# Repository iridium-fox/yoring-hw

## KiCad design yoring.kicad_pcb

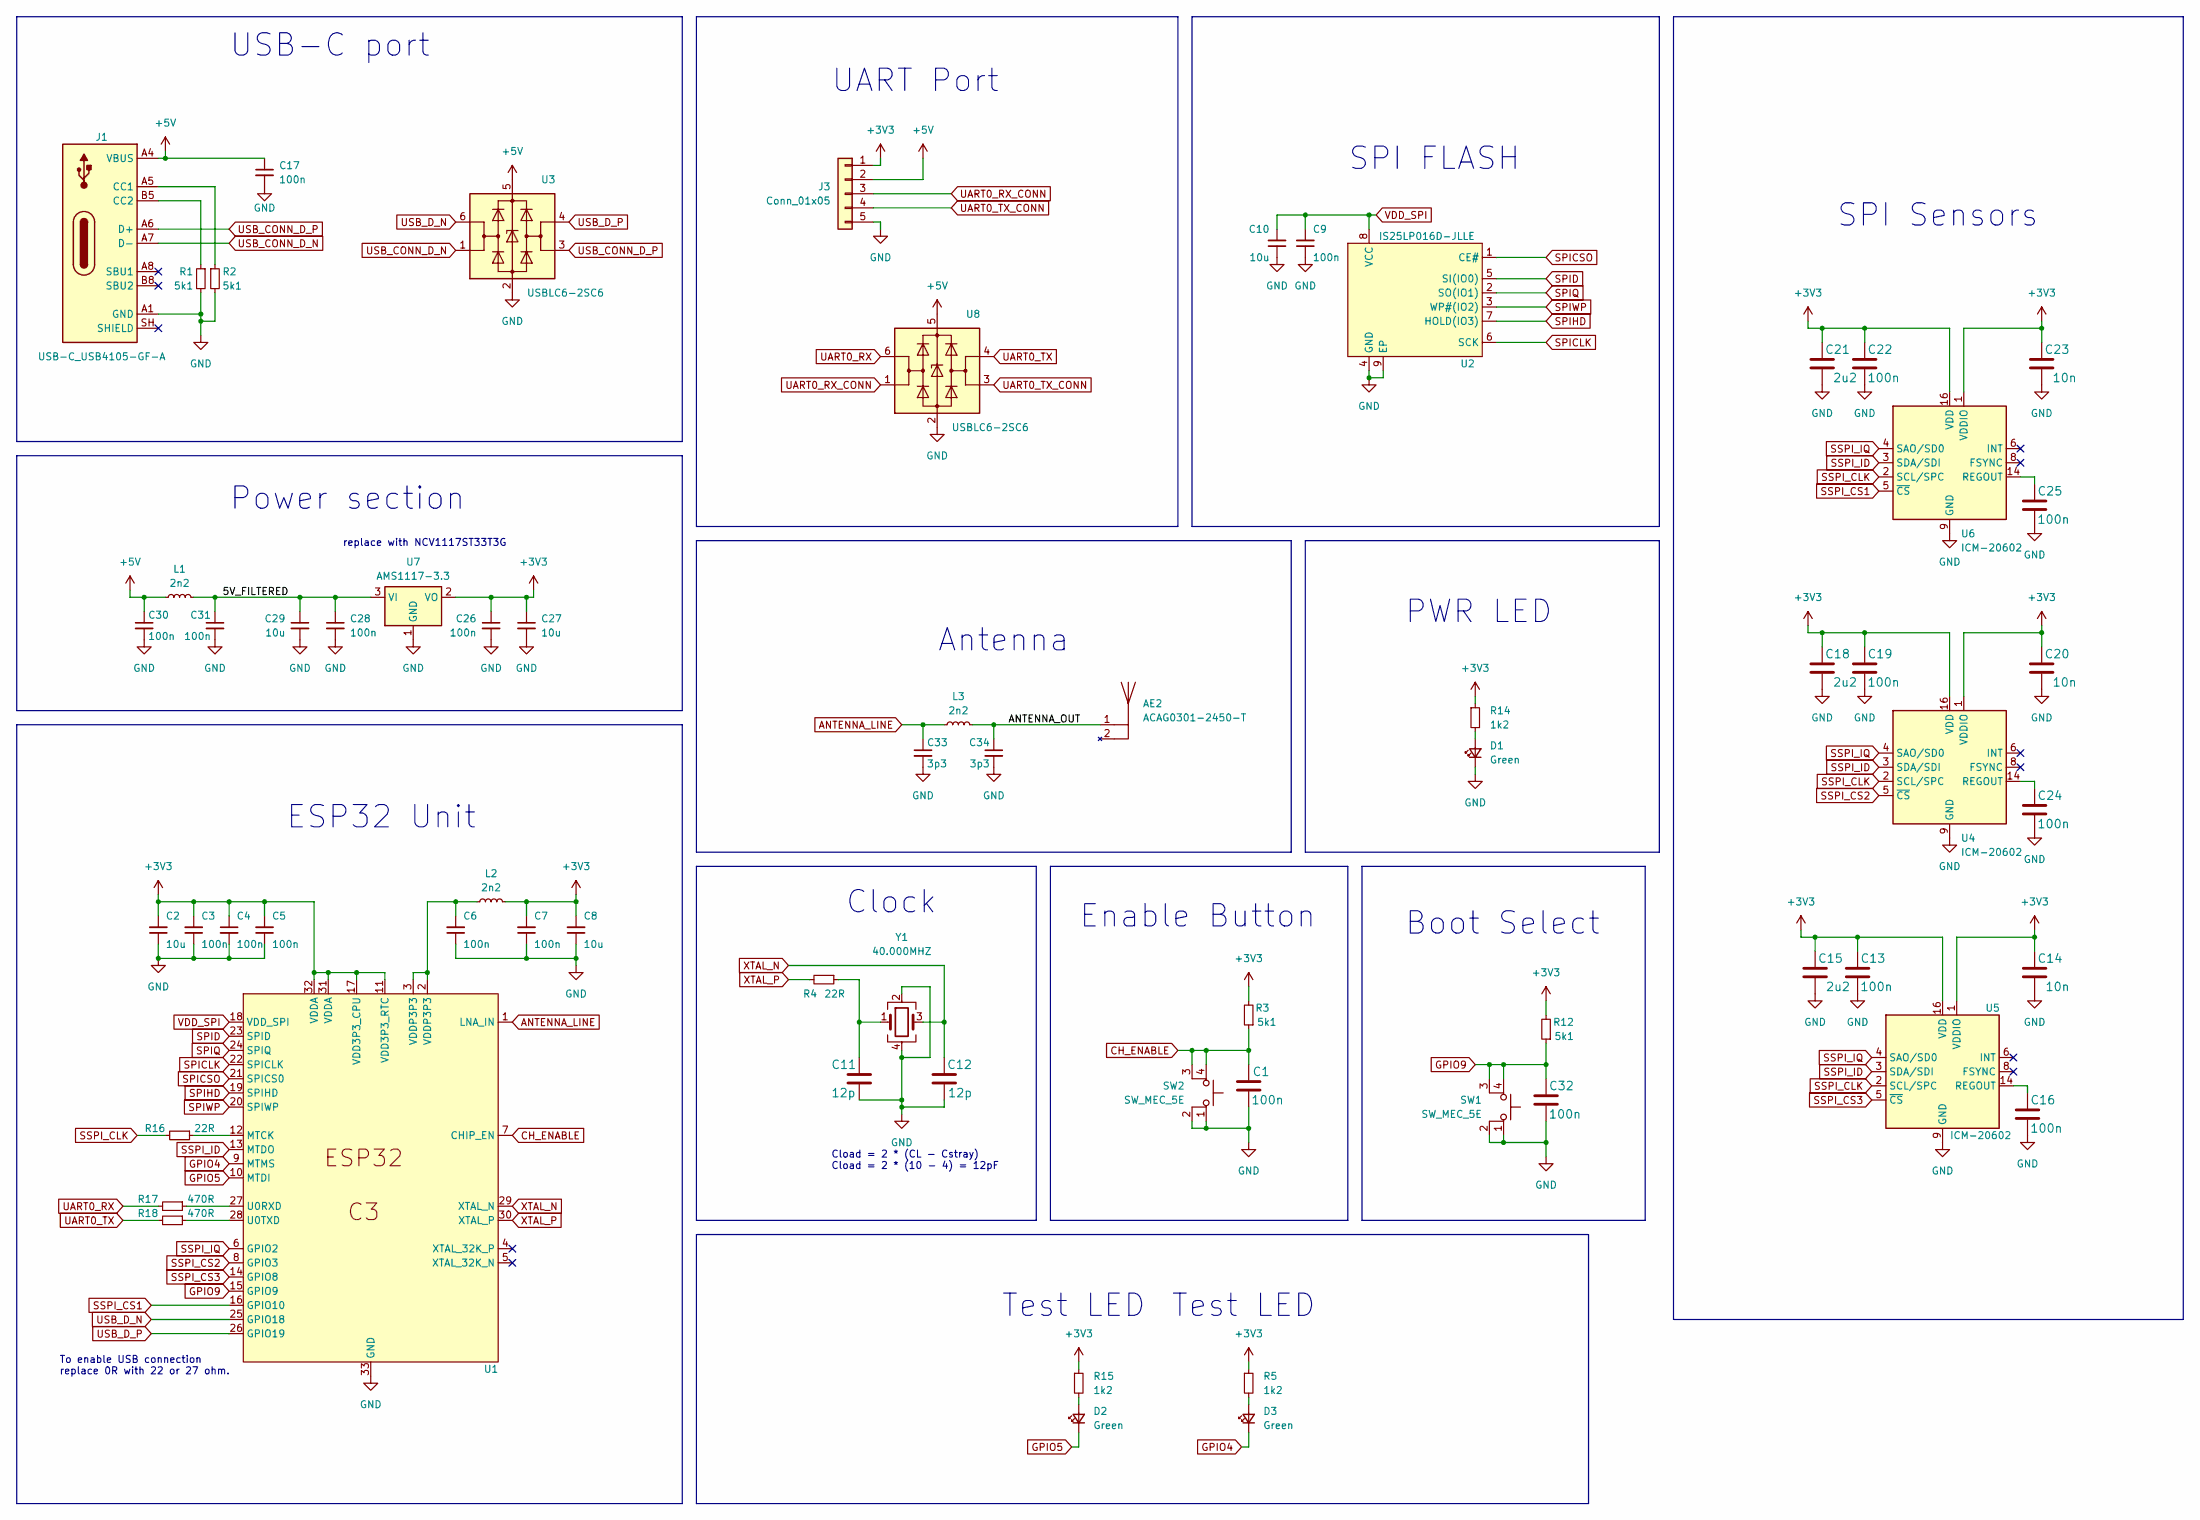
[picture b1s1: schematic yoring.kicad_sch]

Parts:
AE2: ACAG0301-2450-T; ANTC3216X130N
C1, C3, C4, C5, C6, C7, C9, C13, C16, C17, C19, C22, C24, C25, C26, C28, C30, C31, C32: 100n; C_0402_1005Metric_Pad0.74x0.62mm_HandSolder
C2, C8, C10, C27, C29: 10u; C_0603_1608Metric_Pad1.08x0.95mm_HandSolder
C11, C12: 12p; C_0402_1005Metric_Pad0.74x0.62mm_HandSolder
C14, C20, C23: 10n; C_0402_1005Metric_Pad0.74x0.62mm_HandSolder
C15, C18, C21: 2u2; C_0402_1005Metric_Pad0.74x0.62mm_HandSolder
C33, C34: 3p3; C_0402_1005Metric_Pad0.74x0.62mm_HandSolder
D1, D2, D3: Green; LED_0603_1608Metric_Pad1.05x0.95mm_HandSolder
J1: USB-C_USB4105-GF-A; USB-C_GCT_USB4105-GF-A; MPN USB4105-GF-A
J3: Conn_01x05; PinHeader_1x05_P2.54mm_Vertical
L1, L2, L3: 2n2; L_0402_1005Metric_Pad0.77x0.64mm_HandSolder
R1, R2, R3, R12: 5k1; R_0402_1005Metric_Pad0.72x0.64mm_HandSolder
R4, R16: 22R; R_0402_1005Metric_Pad0.72x0.64mm_HandSolder
R5, R14, R15: 1k2; R_0402_1005Metric_Pad0.72x0.64mm_HandSolder
R17, R18: 470R; R_0402_1005Metric_Pad0.72x0.64mm_HandSolder
SW1, SW2: SW_MEC_5E; SW_PUSH_6mm_H5mm
U1: ESP32C3; QFN50P500X500X80-33N; MPN ESP32-C3
U2: IS25LP016D-JLLE; WSON8_8060_IS25LP_ISI; MPN IS25LP016D-JLLE
U3, U8: USBLC6-2SC6; SOT-23-6
U4, U5, U6: ICM-20602; LGA-16_3x3mm_P0.5mm_LayoutBorder3x5y
U7: AMS1117-3.3; SOT-223-3_TabPin2
Y1: 40.000MHZ; ABM810000MHZ12D2W; MPN ABM8-40.000MHZ-10-B1X-T

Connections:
+3V3: C2.2, C3.2, C4.1, C5.2, C7.2, C8.2, C13.2, C14.2, C15.2, C18.2, C19.2, C20.2, C21.2, C22.2, C23.2, C26.1, C27.1, J3.1, L2.2, R3.2, R5.1, R12.2, R14.1, R15.1, U1.11 (VDD3P3_RTC), U1.17 (VDD3P3_CPU), U1.31 (VDDA), U1.32 (VDDA), U4.1 (VDDIO), U4.16 (VDD), U5.1 (VDDIO), U5.16 (VDD), U6.1 (VDDIO), U6.16 (VDD), U7.2 (VO)
+5V: C17.1, C30.1, J1.A4 (VBUS), J1.A9 (VBUS), J1.B4 (VBUS), J1.B9 (VBUS), J3.2, L1.1, U3.5 (VBUS), U8.5 (VBUS)
/5V_FILTERED: C28.1, C29.1, C31.1, L1.2, U7.3 (VI)
/ANTENNA_OUT: AE2.1, C34.1, L3.2
ANTENNA_LINE: C33.1, L3.1, U1.1 (LNA_IN)
CH_ENABLE: C1.2, R3.1, SW2.3 (K), SW2.4 (A), U1.7 (CHIP_EN)
GND: C1.1, C2.1, C3.1, C4.2, C5.1, C6.1, C7.1, C8.1, C9.1, C10.1, C11.1, C12.1, C13.1, C14.1, C15.1, C16.1, C17.2, C18.1, C19.1, C20.1, C21.1, C22.1, C23.1, C24.1, C25.1, C26.2, C27.2, C28.2, C29.2, C30.2, C31.2, C32.1, C33.2, C34.2, D1.1 (K), J1.A1 (GND), J1.A12 (GND), J1.B1 (GND), J1.B12 (GND), J3.5, R1.2, R2.2, SW1.1, SW1.2, SW2.1, SW2.2, U1.33 (GND), U2.4 (GND), U2.9 (EP), U3.2 (GND), U4.9 (GND), U4.10 (GND), U4.11 (GND), U4.12 (GND), U4.13 (GND), U4.15 (GND), U5.9 (GND), U5.10 (GND), U5.11 (GND), U5.12 (GND), U5.13 (GND), U5.15 (GND), U6.9 (GND), U6.10 (GND), U6.11 (GND), U6.12 (GND), U6.13 (GND), U6.15 (GND), U7.1 (GND), U8.2 (GND), Y1.2, Y1.4
GPIO4: D3.1 (K), U1.9 (MTMS)
GPIO5: D2.1 (K), U1.10 (MTDI)
GPIO9: C32.2, R12.1, SW1.3 (K), SW1.4 (A), U1.15 (GPIO9)
unnamed: C6.2, L2.1, U1.2 (VDDP3P3), U1.3 (VDDP3P3)
unnamed: C11.2, R4.1, Y1.1
unnamed: D1.2 (A), R14.2
unnamed: D2.2 (A), R15.2
unnamed: D3.2 (A), R5.2
unnamed: J1.A5 (CC1), R2.1
unnamed: J1.B5 (CC2), R1.1
unnamed: R16.1, U1.12 (MTCK)
unnamed: R17.1, U1.27 (U0RXD)
unnamed: R18.1, U1.28 (U0TXD)
unnamed: C24.2, U4.14 (REGOUT)
unnamed: C16.2, U5.14 (REGOUT)
unnamed: C25.2, U6.14 (REGOUT)
SPICLK: U1.22 (SPICLK), U2.6 (SCK)
SPICSO: U1.21 (SPICS0), U2.1 (CE#)
SPID: U1.23 (SPID), U2.5 (SI(IO0))
SPIHD: U1.19 (SPIHD), U2.7 (HOLD(IO3))
SPIQ: U1.24 (SPIQ), U2.2 (SO(IO1))
SPIWP: U1.20 (SPIWP), U2.3 (WP#(IO2))
SSPI_CLK: R16.2, U4.2 (SCL/SPC), U5.2 (SCL/SPC), U6.2 (SCL/SPC)
SSPI_CS1: U1.16 (GPIO10), U6.5 (~CS)
SSPI_CS2: U1.8 (GPIO3), U4.5 (~CS)
SSPI_CS3: U1.14 (GPIO8), U5.5 (~CS)
SSPI_ID: U1.13 (MTDO), U4.3 (SDA/SDI), U5.3 (SDA/SDI), U6.3 (SDA/SDI)
SSPI_IQ: U1.6 (GPIO2), U4.4 (SAO/SD0), U5.4 (SAO/SD0), U6.4 (SAO/SD0)
UART0_RX: R17.2, U8.6 (I/O1)
UART0_RX_CONN: J3.3, U8.1 (I/O1)
UART0_TX: R18.2, U8.4 (I/O2)
UART0_TX_CONN: J3.4, U8.3 (I/O2)
USB_CONN_D_N: J1.A7 (D-), J1.B7 (D-), U3.1 (I/O1)
USB_CONN_D_P: J1.A6 (D+), J1.B6 (D+), U3.3 (I/O2)
USB_D_N: U1.25 (GPIO18), U3.6 (I/O1)
USB_D_P: U1.26 (GPIO19), U3.4 (I/O2)
VDD_SPI: C9.2, C10.2, U1.18 (VDD_SPI), U2.8 (VCC)
XTAL_N: C12.2, U1.29 (XTAL_N), Y1.3
XTAL_P: R4.2, U1.30 (XTAL_P)

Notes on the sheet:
To enable USB connection replace 0R with 22 or 27 ohm.
Clock
Cload = 2 * (CL - Cstray) Cload = 2 * (10 - 4) = 12pF
Antenna
Test LED
ESP32 Unit
Boot Select
SPI FLASH
UART Port
replace with NCV1117ST33T3G
Enable Button
USB-C port
Power section
PWR LED
SPI Sensors

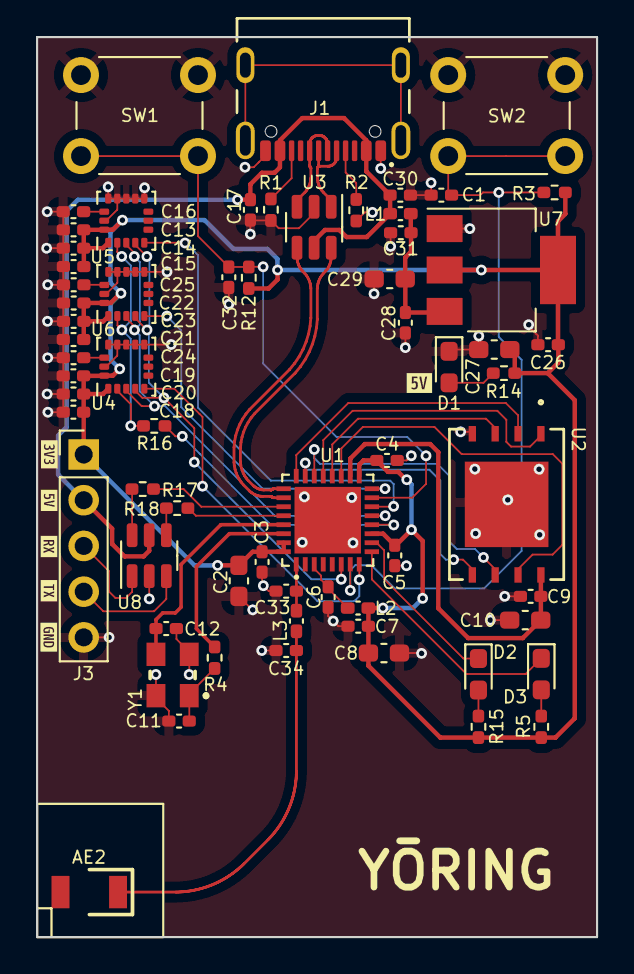
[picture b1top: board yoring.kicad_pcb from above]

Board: 4 copper layers, 31.1 x 50.0 mm, 71 parts (0 on the bottom side), 46 nets.

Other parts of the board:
kibuzzard-64F249A3: G***; kibuzzard-64F249A3
kibuzzard-64F249B1: G***; kibuzzard-64F249B1
kibuzzard-64F249BD: G***; kibuzzard-64F249BD
kibuzzard-64F24942: G***; kibuzzard-64F24942
kibuzzard-64F24971: G***; kibuzzard-64F24971
kibuzzard-64F24993: G***; kibuzzard-64F24993

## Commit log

2025-11-18 Commit before local repo deletion

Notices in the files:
parts and their libraries:
License: Apache-2.0
